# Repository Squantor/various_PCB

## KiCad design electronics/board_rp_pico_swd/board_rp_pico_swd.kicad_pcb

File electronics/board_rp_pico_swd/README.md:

# Raspberry Pi Pico SWD adapter board
The three pin connection of the raspberry pi pico board is inconvienient to say the least. This will break it out to a standard 10 pin ARM SWD/JTAG connection
## TODO's
Still some things need to be done:
* PCB layout
* Review with one night in between
* Produce at [OSHPARK](https://oshpark.com/)
* Assemble
* Test & characterise
* update Readme.md with pictures and BOM
## BOM
* 2*5 1.27mm pitch header
* 3 pin 2.54mm pitch angled female header

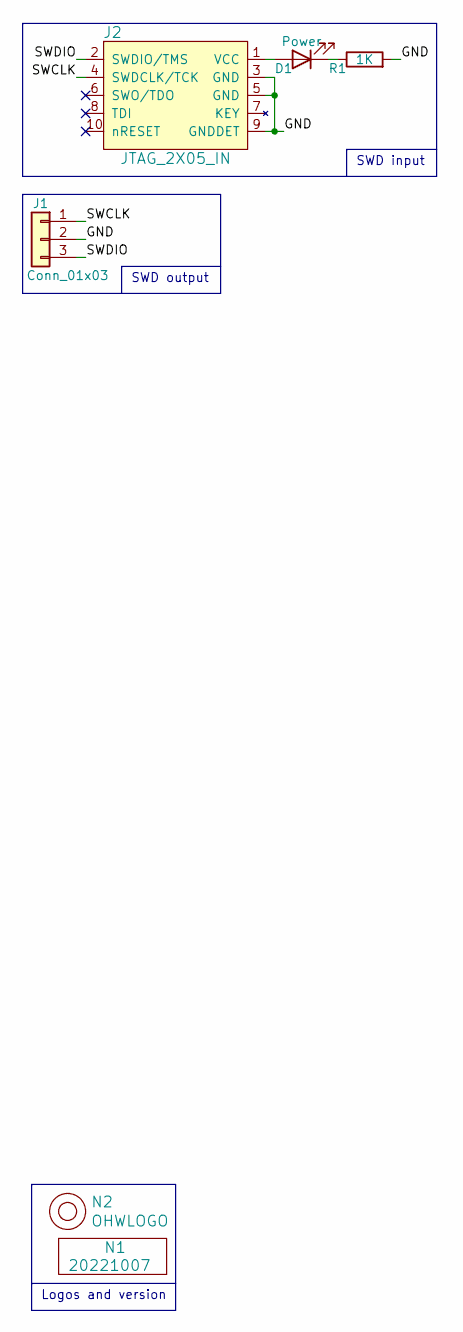
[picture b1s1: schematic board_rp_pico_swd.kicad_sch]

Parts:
D1: Power; LED_0603_hand
J1: Conn_01x03; PinSocket_1x03_P2.54mm_Vertical
J2: JTAG_2X05_IN; Header-0127-2X05-SMD
N1: 20221007; Label_Generic
N2: OHWLOGO; OSHW-Symbol_6.7x6mm_SilkScreen
R1: 1K; R_0603_hand

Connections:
/GND: J1.2, J2.3 (GND), J2.5 (GND), J2.9 (GNDDET), R1.2
/SWCLK: J1.1, J2.4 (SWDCLK/TCK)
/SWDIO: J1.3, J2.2 (SWDIO/TMS)
unnamed: D1.1 (K), R1.1
unnamed: D1.2 (A), J2.1 (VCC)

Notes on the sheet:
Logos and version
SWD input
SWD output

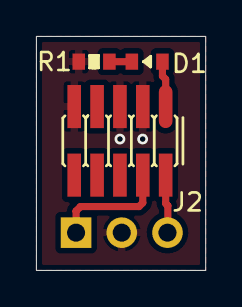
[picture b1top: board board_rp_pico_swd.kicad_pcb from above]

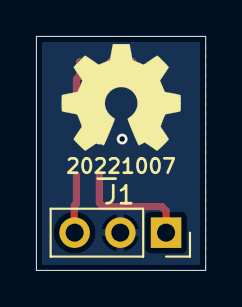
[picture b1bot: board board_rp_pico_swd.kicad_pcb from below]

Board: 2 copper layers, 9.4 x 13.0 mm, 6 parts (3 on the bottom side), 5 nets.

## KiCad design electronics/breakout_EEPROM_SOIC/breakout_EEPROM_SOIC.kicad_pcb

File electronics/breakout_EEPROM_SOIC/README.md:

# SOIC EEPROM breakout
Breakout board for SOIC I2C EEPROMs.
## TODO's
Still some things need to be done:
* Review with one night in between
* Produce
* Assemble
* Test & characterise
* update Readme.md with pictures and BOM
## BOM
* Any 24XX I2C EEPROM in SOIC probably fits here.

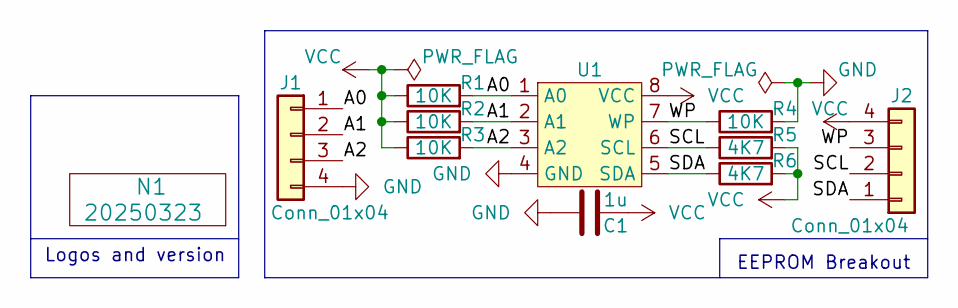
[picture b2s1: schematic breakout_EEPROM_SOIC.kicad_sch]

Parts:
C1: 1u; C_0603
J1, J2: Conn_01x04; Header-0254-1X04-H010
N1: 20250323; Label_Generic
R1, R2, R3, R4: 10K; R_0603_hand
R5, R6: 4K7; R_0603_hand
U1: SOIC-8

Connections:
/A0: J1.1, R1.2, U1.1 (A0)
/A1: J1.2, R2.2, U1.2 (A1)
/A2: J1.3, R3.2, U1.3 (A2)
/SCL: J2.2, R5.1, U1.6 (SCL)
/SDA: J2.1, R6.1, U1.5 (SDA)
/WP: J2.3, R4.1, U1.7 (WP)
GND: C1.1, J1.4, R4.2, U1.4 (GND)
VCC: C1.2, J2.4, R1.1, R2.1, R3.1, R5.2, R6.2, U1.8 (VCC)

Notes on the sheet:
EEPROM Breakout
Logos and version

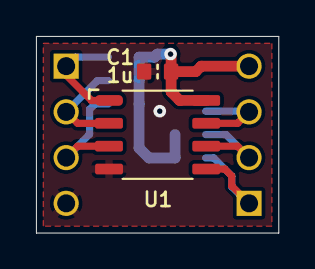
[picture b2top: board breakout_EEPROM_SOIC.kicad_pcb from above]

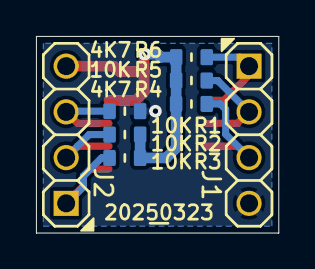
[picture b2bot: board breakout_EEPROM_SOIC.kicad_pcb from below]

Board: 2 copper layers, 13.5 x 10.9 mm, 11 parts (9 on the bottom side), 8 nets.

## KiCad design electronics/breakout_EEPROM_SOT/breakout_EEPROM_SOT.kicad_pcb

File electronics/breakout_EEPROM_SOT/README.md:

# breakout module for SOT I2C EEPROM
Breakout module for SOT footprint I2C EEPROMS
## TODO's
Still some things need to be done:
* Review with one night in between
* Produce at [OSHPARK](https://oshpark.com/)
* Assemble
* Test & characterise
* update Readme.md with pictures and BOM
## BOM
This is a list of hardware components. If just mentioned a generic component like a 1K 0402 resistor, just name it as such, free to substitute. If you need some special integrated IC's show some sources like Mouser, Digikey, Farnell, or LCSC
* Generic I2C EEPROM

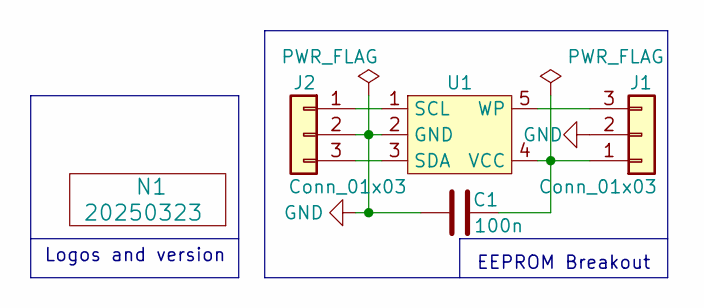
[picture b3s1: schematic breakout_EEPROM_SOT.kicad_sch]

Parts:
C1: 100n; C_0603
J1, J2: Conn_01x03; Header-0254-1X03-H008
N1: 20250323; Label_Generic
U1: SOT25-diodesinc

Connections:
GND: C1.1, J1.2, J2.2, U1.2 (GND)
unnamed: C1.2, J1.1, U1.4 (VCC)
unnamed: J1.3, U1.5 (WP)
unnamed: J2.1, U1.1 (SCL)
unnamed: J2.3, U1.3 (SDA)

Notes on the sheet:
Logos and version
EEPROM Breakout

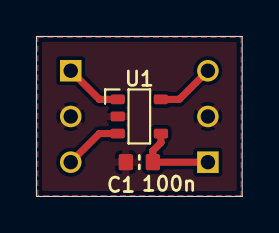
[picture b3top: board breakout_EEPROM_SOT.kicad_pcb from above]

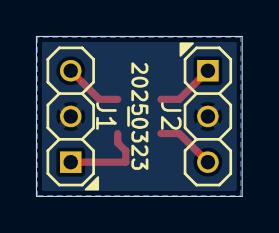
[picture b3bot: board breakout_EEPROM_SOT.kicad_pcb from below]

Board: 2 copper layers, 11.4 x 8.9 mm, 5 parts (3 on the bottom side), 5 nets.

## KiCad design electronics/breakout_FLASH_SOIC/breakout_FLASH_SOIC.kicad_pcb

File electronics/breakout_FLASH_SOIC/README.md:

# SOIC flash breakout
Simple breakout board for SOIC serial flashes of the 25 series. Usable for normal and wide flash SOIC footprints. Has pullup for CE and pulldown SCK
## TODO's
Still some things need to be done:
* Review with one night in between
* Produce
* Assemble
* Test & characterise
* update Readme.md with pictures and BOM
## BOM
* SOIC or SOIC-W serial flash of the 25 series.

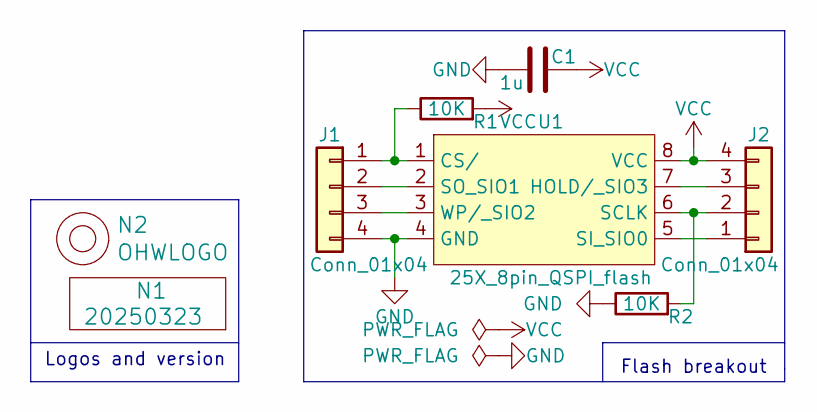
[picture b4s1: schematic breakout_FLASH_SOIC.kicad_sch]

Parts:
C1: 1u; C_0603
J1, J2: Conn_01x04; Header-0254-1X04-H010
N1: 20250323; Label_Generic
N2: OHWLOGO; OSHW-Symbol_6.7x6mm_SilkScreen
R1, R2: 10K; R_0603_hand
U1: 25X_8pin_QSPI_flash; SOIC-8_dual_wide

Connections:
GND: C1.1, J1.4, R2.1, U1.4 (GND)
unnamed: J1.1, R1.1, U1.1 (CS/)
unnamed: J1.2, U1.2 (SO_SIO1)
unnamed: J1.3, U1.3 (WP/_SIO2)
unnamed: J2.1, U1.5 (SI_SIO0)
unnamed: J2.2, R2.2, U1.6 (SCLK)
unnamed: J2.3, U1.7 (HOLD/_SIO3)
VCC: C1.2, J2.4, R1.2, U1.8 (VCC)

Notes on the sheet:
Flash breakout
Logos and version

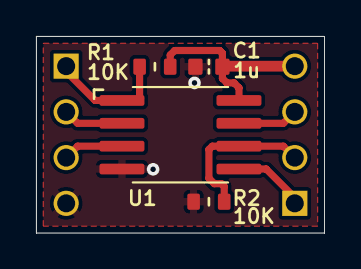
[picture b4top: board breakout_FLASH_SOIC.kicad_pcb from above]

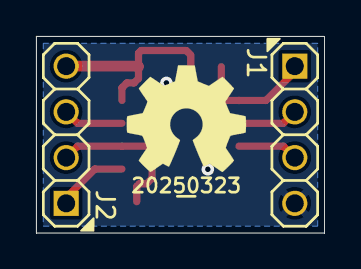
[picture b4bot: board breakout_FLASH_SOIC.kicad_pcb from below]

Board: 2 copper layers, 16.0 x 10.9 mm, 8 parts (4 on the bottom side), 8 nets.

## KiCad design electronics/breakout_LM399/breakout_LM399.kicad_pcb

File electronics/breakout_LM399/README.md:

# LM399 breakout
Very simple breakout for the LM399 voltage reference to check the footprint (And cutouts)
## TODO's
* Produce at [OSHPARK](https://oshpark.com/)
* Assemble
* Test & characterise
* update Readme.md with pictures and BOM
## BOM
* [LM399](https://www.analog.com/media/en/technical-documentation/data-sheets/199399fc.pdf) voltage reference

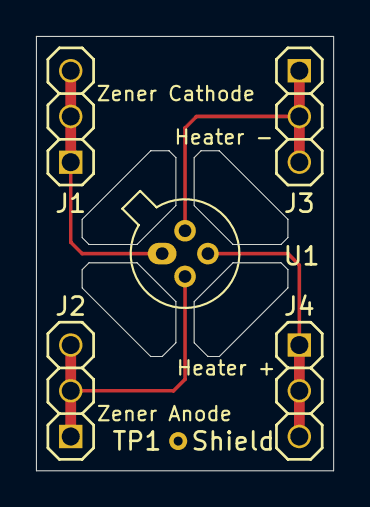
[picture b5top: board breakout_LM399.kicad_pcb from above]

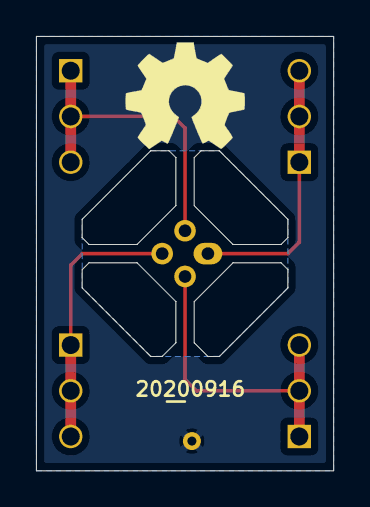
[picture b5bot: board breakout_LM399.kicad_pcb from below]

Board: 2 copper layers, 16.5 x 24.1 mm, 8 parts (2 on the bottom side), 4 nets.

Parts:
J1, J2, J3, J4: Conn_01x03; Header-0254-1X03-H010
N1: 20200916; Label_Generic
N2: OHWLOGO; OSHW-Symbol_6.7x6mm_SilkScreen
TP1: Shield; TestPoint_hole_H05R10
U1: LM399; TO-46-4

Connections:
/Heater+: J4.1, J4.2, J4.3, U1.3
/Heater-: J3.1, J3.2, J3.3, U1.4
/ZenerA: J2.1, J2.2, J2.3, U1.2
/ZenerC: J1.1, J1.2, J1.3, U1.1
